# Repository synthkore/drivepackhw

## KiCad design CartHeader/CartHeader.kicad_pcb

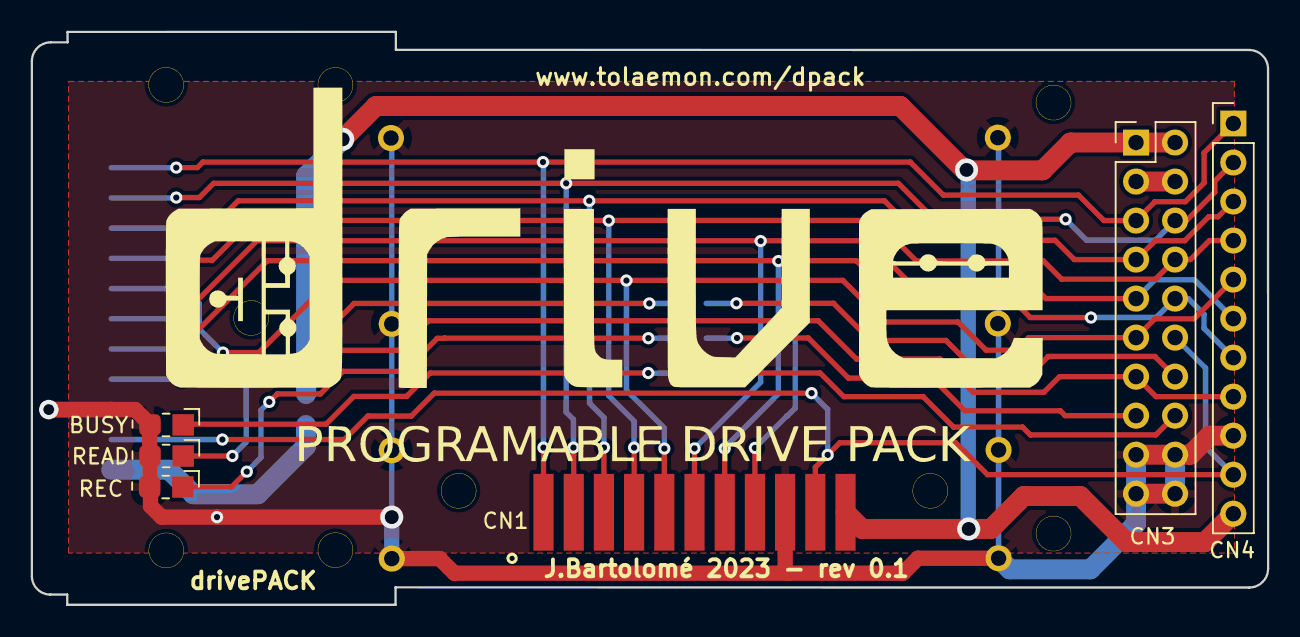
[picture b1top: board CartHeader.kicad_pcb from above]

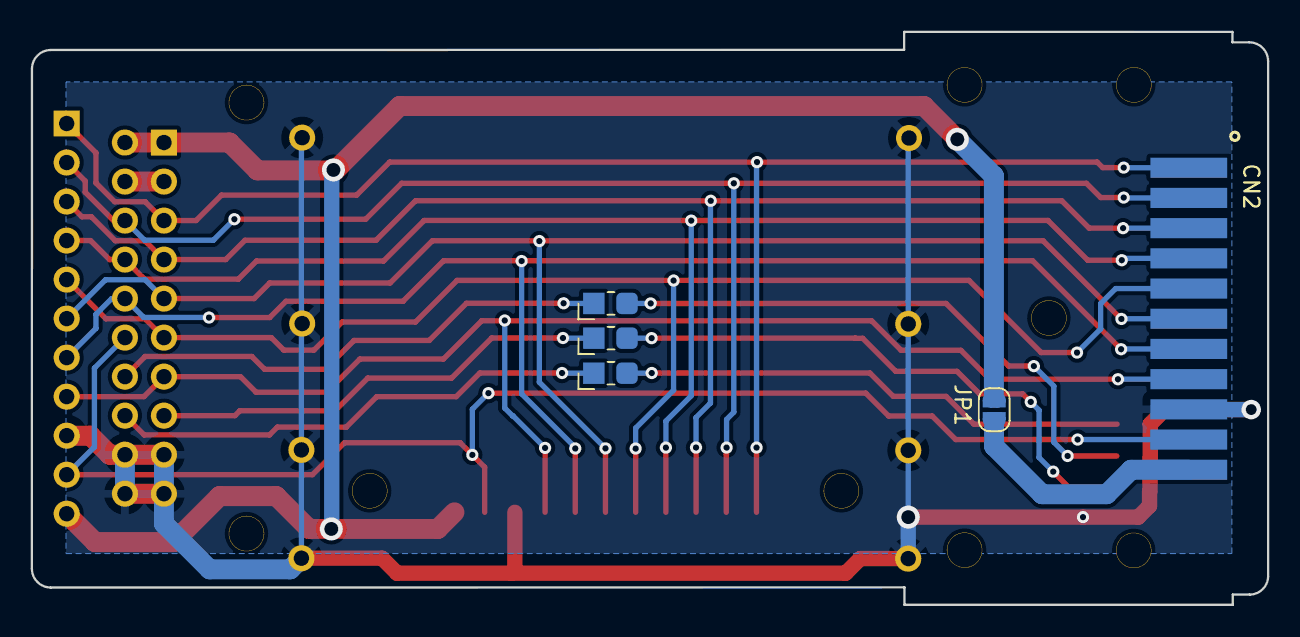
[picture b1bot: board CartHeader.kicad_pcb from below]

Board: 2 copper layers, 80.5 x 37.3 mm, 28 parts (5 on the bottom side), 19 nets.

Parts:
BUSY: LD; SMD_LD_0805_2012Metric
CN1: dumper connector; DrivePackHeaderFemale
CN2: drivePACKconnector; DrivePackHeaderMale
CN3: PinStrip2x10; PinHeader_2x10_P2.54mm_Vertical
CN4: PinStrip11; PinHeader_1x11_P2.54mm_Vertical
CN5, CN6, CN7, CN8, CN9, CN10, CN11, CN12: Pin; PinPad_1x01_P2.54mm_Round
JP1: Jumper; SolderJumper-2_P1.3mm_Open_RoundedPad1.0x1.5mm
MH1, MH2, MH3, MH4, MH5, MH6, MH7, MH8, MH9: MountingHole; MHole_2_25
R1, R2, R3: 150; SMD_R_0805_2012Metric
READ: LD; SMD_LD_0805_2012Metric
REC: LD; SMD_LD_0805_2012Metric

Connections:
/!CS: CN1.10 (nCS), CN2.10 (nCS), CN3.12, CN4.10
/!D0: CN1.4 (nD0), CN2.4 (nD0), CN3.8, CN4.4
/!D1: CN1.3 (nD1), CN2.3 (nD1), CN3.7, CN4.3
/!D2: CN1.2 (nD2), CN2.2 (nD2), CN3.6, CN4.2
/!D3: CN1.1 (nD3), CN2.1 (nD3), CN3.5, CN4.1
/!W\R: CN1.5 (RnW), CN2.5 (RnW), CN3.11, CN4.5
/?: CN1.8 (?), CN2.8 (?), CN3.13, CN4.8
/CLCK1: CN1.6 (CLK1), CN2.6 (CLK1), CN3.9, CN4.6
/CLCK2: CN1.7 (CLK2), CN2.7 (CLK2), CN3.10, CN4.7
/ROM_IO1: CN3.14, R1.1
/ROM_IO2: CN3.15, R2.1
/ROM_IO3: CN3.16, R3.1
GND: BUSY.2, CN1.9 (GND), CN2.9 (GND), CN3.17, CN3.18, CN3.19, CN3.20, CN4.9, CN5.1, CN6.1, CN7.1, CN8.1, CN9.1, CN10.1, CN11.1, CN12.1, READ.2, REC.2
unnamed: CN2.11 (Vcc), JP1.1
unnamed: R1.2, READ.1
unnamed: R2.2, REC.1
unnamed: BUSY.1, R3.2
VCC3.3: CN3.3, CN3.4
VCC5: CN1.11 (Vcc), CN3.1, CN3.2, CN4.11, JP1.2

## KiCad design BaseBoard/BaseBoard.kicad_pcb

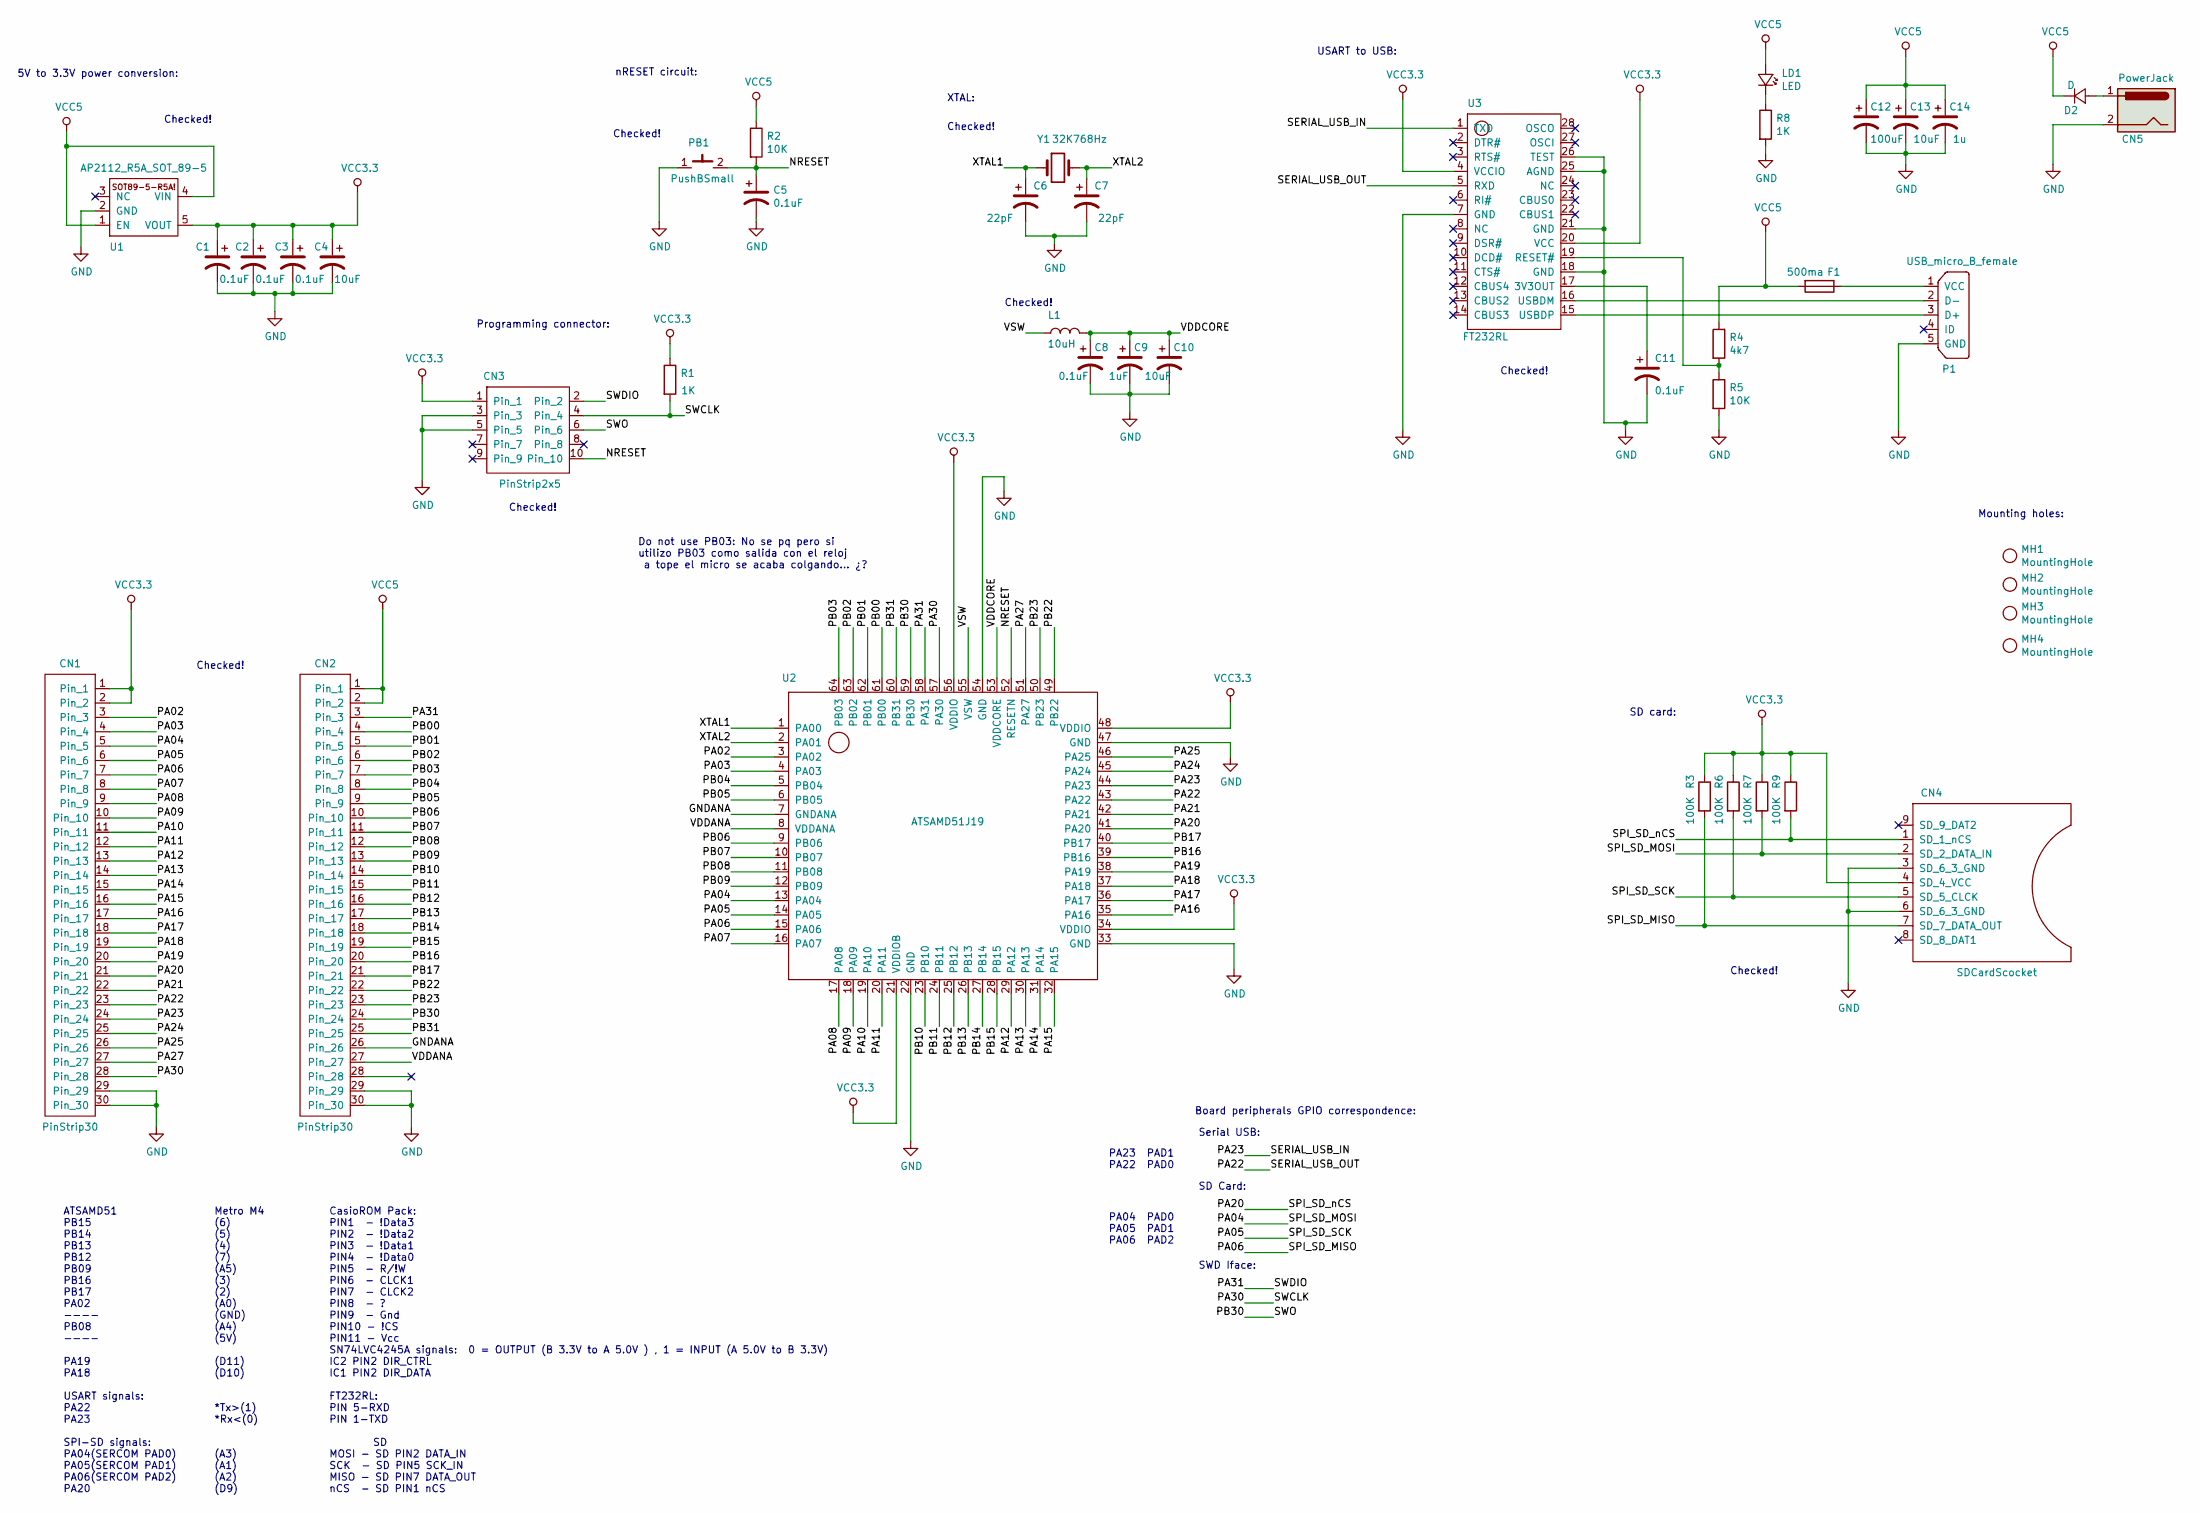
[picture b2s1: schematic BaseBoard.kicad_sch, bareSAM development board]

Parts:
C1, C2, C3, C5, C8, C11: 0.1uF; SMD_C_0805_2012Metric
C4, C10, C13: 10uF; SMD_C_0.5x0.5cm
C6, C7: 22pF; SMD_C_0805_2012Metric
C9: 1uF; SMD_C_0.5x0.5cm
C12: 100uF; SMD_C_0.5x0.5cm
C14: 1u; SMD_C_0.5x0.5cm
CN1, CN2: PinStrip30; PinHeader_1x30_P2.54mm_Vertical
CN3: PinStrip2x5; PinHeader_2x05_P2.54mm_Vertical
CN4: SDCardScocket; SDCard_NoHoles
CN5: PowerJack; PowerFemale
D2: D; D_SOD-123
F1: 500ma; SMD_C_0805_2012Metric
L1: 10uH; SMD_L_4018
LD1: LED; SMD_LD_0805_2012Metric
MH1, MH2, MH3, MH4: MountingHole
P1: USB_micro_B_female; USB_Micro-B_Wuerth_629105150521
PB1: PushBSmall; PushButton
R1, R8: 1K; SMD_R_0805_2012Metric
R2, R5: 10K; SMD_R_0805_2012Metric
R3, R6, R7, R9: 100K; SMD_R_0805_2012Metric
R4: 4k7; SMD_R_0805_2012Metric
U1: AP2112_R5A_SOT_89-5; SOT-89-5_Handsoldering
U2: ATSAMD51J19; TQFP-64-1EP_10x10mm_P0.5mm_EP8x8mm
U3: FT232RL; SSOP-28_5.3x10.2mm_P0.65mm
Y1: 32K768Hz; SMD_XTAL_3.4x2.7max

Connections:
/GNDANA: CN2.26, U2.7 (GNDANA)
/NRESET: C5.1, CN3.10, PB1.2, R2.2, U2.52 (RESETN)
/PA02: CN1.3, U2.3 (PA02)
/PA03: CN1.4, U2.4 (PA03)
/PA04: CN1.5, CN4.2 (SD_2_DATA_IN), R7.2, U2.13 (PA04)
/PA05: CN1.6, CN4.5 (SD_5_CLCK), R6.2, U2.14 (PA05)
/PA06: CN1.7, CN4.7 (SD_7_DATA_OUT), R3.2, U2.15 (PA06)
/PA07: CN1.8, U2.16 (PA07)
/PA08: CN1.9, U2.17 (PA08)
/PA09: CN1.10, U2.18 (PA09)
/PA10: CN1.11, U2.19 (PA10)
/PA11: CN1.12, U2.20 (PA11)
/PA12: CN1.13, U2.29 (PA12)
/PA13: CN1.14, U2.30 (PA13)
/PA14: CN1.15, U2.31 (PA14)
/PA15: CN1.16, U2.32 (PA15)
/PA16: CN1.17, U2.35 (PA16)
/PA17: CN1.18, U2.36 (PA17)
/PA18: CN1.19, U2.37 (PA18)
/PA19: CN1.20, U2.38 (PA19)
/PA20: CN1.21, CN4.1 (SD_1_nCS), R9.2, U2.41 (PA20)
/PA21: CN1.22, U2.42 (PA21)
/PA22: CN1.23, U2.43 (PA22), U3.5 (RXD)
/PA23: CN1.24, U2.44 (PA23), U3.1 (TXD)
/PA24: CN1.25, U2.45 (PA24)
/PA25: CN1.26, U2.46 (PA25)
/PA27: CN1.27, U2.51 (PA27)
/PA30: CN1.28, CN3.4, R1.2, U2.57 (PA30)
/PA31: CN2.3, CN3.2, U2.58 (PA31)
/PB00: CN2.4, U2.61 (PB00)
/PB01: CN2.5, U2.62 (PB01)
/PB02: CN2.6, U2.63 (PB02)
/PB03: CN2.7, U2.64 (PB03)
/PB04: CN2.8, U2.5 (PB04)
/PB05: CN2.9, U2.6 (PB05)
/PB06: CN2.10, U2.9 (PB06)
/PB07: CN2.11, U2.10 (PB07)
/PB08: CN2.12, U2.11 (PB08)
/PB09: CN2.13, U2.12 (PB09)
/PB10: CN2.14, U2.23 (PB10)
/PB11: CN2.15, U2.24 (PB11)
/PB12: CN2.16, U2.25 (PB12)
/PB13: CN2.17, U2.26 (PB13)
/PB14: CN2.18, U2.27 (PB14)
/PB15: CN2.19, U2.28 (PB15)
/PB16: CN2.20, U2.39 (PB16)
/PB17: CN2.21, U2.40 (PB17)
/PB22: CN2.22, U2.49 (PB22)
/PB23: CN2.23, U2.50 (PB23)
/PB30: CN2.24, CN3.6, U2.59 (PB30)
/PB31: CN2.25, U2.60 (PB31)
/VDDANA: CN2.27, U2.8 (VDDANA)
/VDDCORE: C8.1, C9.1, C10.1, L1.1, U2.53 (VDDCORE)
/VSW: L1.2, U2.55 (VSW)
/XTAL1: C6.1, U2.1 (PA00), Y1.1
/XTAL2: C7.1, U2.2 (PA01), Y1.2
GND: C1.2, C2.2, C3.2, C4.2, C5.2, C6.2, C7.2, C8.2, C9.2, C10.2, C11.2, C12.2, C13.2, C14.2, CN1.29, CN1.30, CN2.29, CN2.30, CN3.3, CN3.5, CN4.3 (SD_6_3_GND), CN4.6 (SD_6_3_GND), CN5.2, P1.5 (GND), PB1.1, R5.2, R8.2, U1.2 (GND), U2.22 (GND), U2.33 (GND), U2.47 (GND), U2.54 (GND), U3.7 (GND), U3.18 (GND), U3.21 (GND), U3.25 (AGND), U3.26 (TEST)
unnamed: C11.1, U3.17 (3V3OUT)
unnamed: CN5.1, D2.1
unnamed: F1.1, P1.1 (VCC)
unnamed: LD1.2, R8.1
unnamed: P1.2 (D-), U3.16 (USBDM)
unnamed: P1.3 (D+), U3.15 (USBDP)
unnamed: R4.2, R5.1, U3.19 (RESET#)
VCC3.3: C1.1, C2.1, C3.1, C4.1, CN1.1, CN1.2, CN3.1, CN4.4 (SD_4_VCC), R1.1, R3.1, R6.1, R7.1, R9.1, U1.5 (VOUT), U2.21 (VDDIOB), U2.34 (VDDIO), U2.48 (VDDIO), U2.56 (VDDIO), U3.4 (VCCIO), U3.20 (VCC)
VCC5: C12.1, C13.1, C14.1, CN2.1, CN2.2, D2.2, F1.2, LD1.1, R2.1, R4.1, U1.1 (EN), U1.4 (VIN)

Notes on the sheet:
XTAL:
PA04 PAD0 PA05 PAD1 PA06 PAD2
Do not use PB03: No se pq pero si utilizo PB03 como salida con el reloj a tope el micro se acaba colgando... ¿?
Mounting holes:
Checked!
Metro M4 (6) (5) (4) (7) (A5) (3) (2) (A0) (GND) (A4) (5V) (D11) (D10) *Tx>(1) *Rx<(0) (A3) (A1) (A2) (D9)
CasioROM Pack: PIN1 - !Data3 PIN2 - !Data2 PIN3 - !Data1 PIN4 - !Data0 PIN5 - R/!W PIN6 - CLCK1 PIN7 - CLCK2 PIN8 - ? PIN9 - Gnd PIN10 - !CS PIN11 - Vcc SN74LVC4245A signals: 0 = OUTPUT (B 3.3V to A 5.0V ) , 1 = INPUT (A 5.0V to B 3.3V) IC2 PIN2 DIR_CTRL IC1 PIN2 DIR_DATA FT232RL: PIN 5-RXD PIN 1-T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
Board peripherals GPIO correspondence:
5V to 3.3V power conversion:
SWD Iface:
PA23 PAD1 PA22 PAD0
Serial USB:
USART to USB:
Programming connector:
SD Card:
ATSAMD51 PB15 PB14 PB13 PB12 PB09 PB16 PB17 PA02 ---- PB08 ---- PA19 PA18 USART signals: PA22 PA23 SPI-SD signals: PA04(SERCOM PAD0) PA05(SERCOM PAD1) PA06(SERCOM PAD2) PA20
nRESET circuit:
SD card:

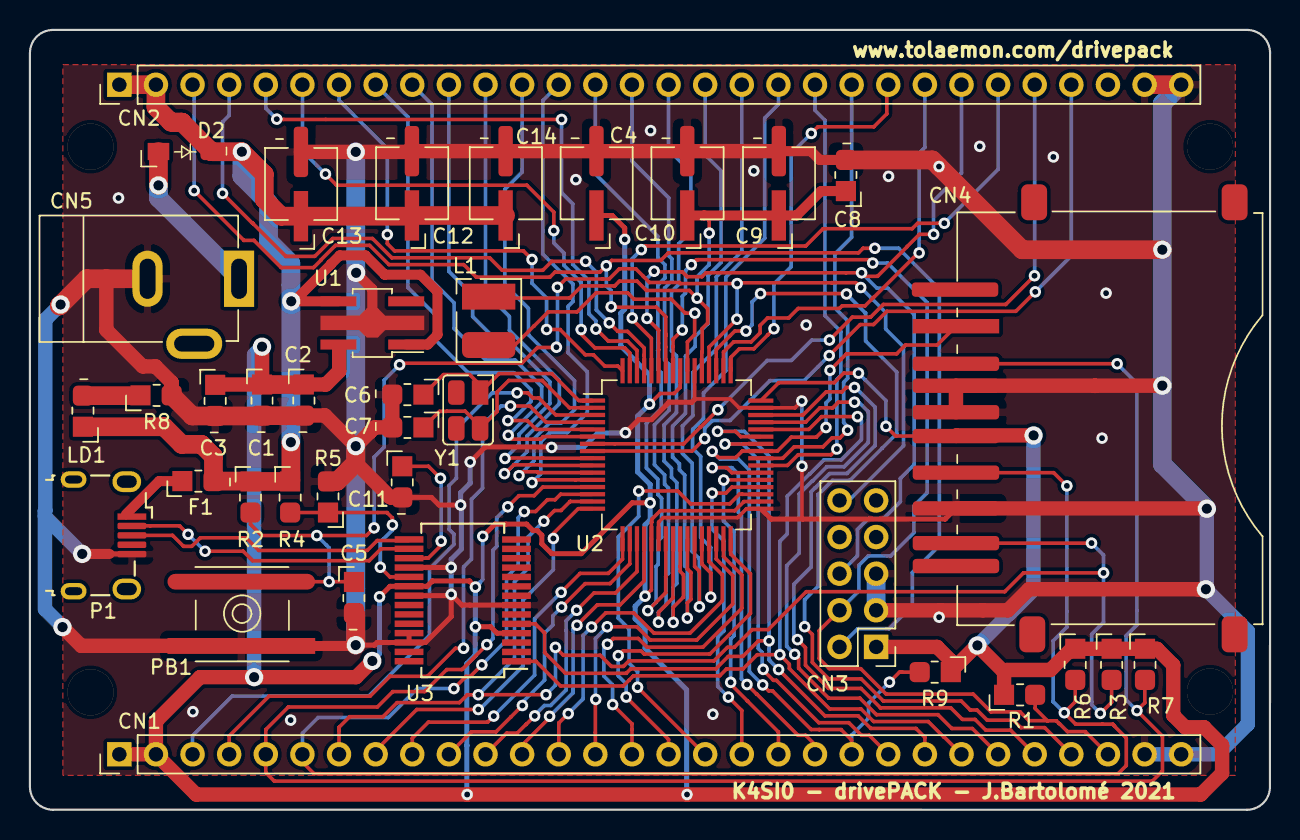
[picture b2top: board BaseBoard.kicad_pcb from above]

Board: 2 copper layers, 86.0 x 54.1 mm, 42 parts (0 on the bottom side), 66 nets.

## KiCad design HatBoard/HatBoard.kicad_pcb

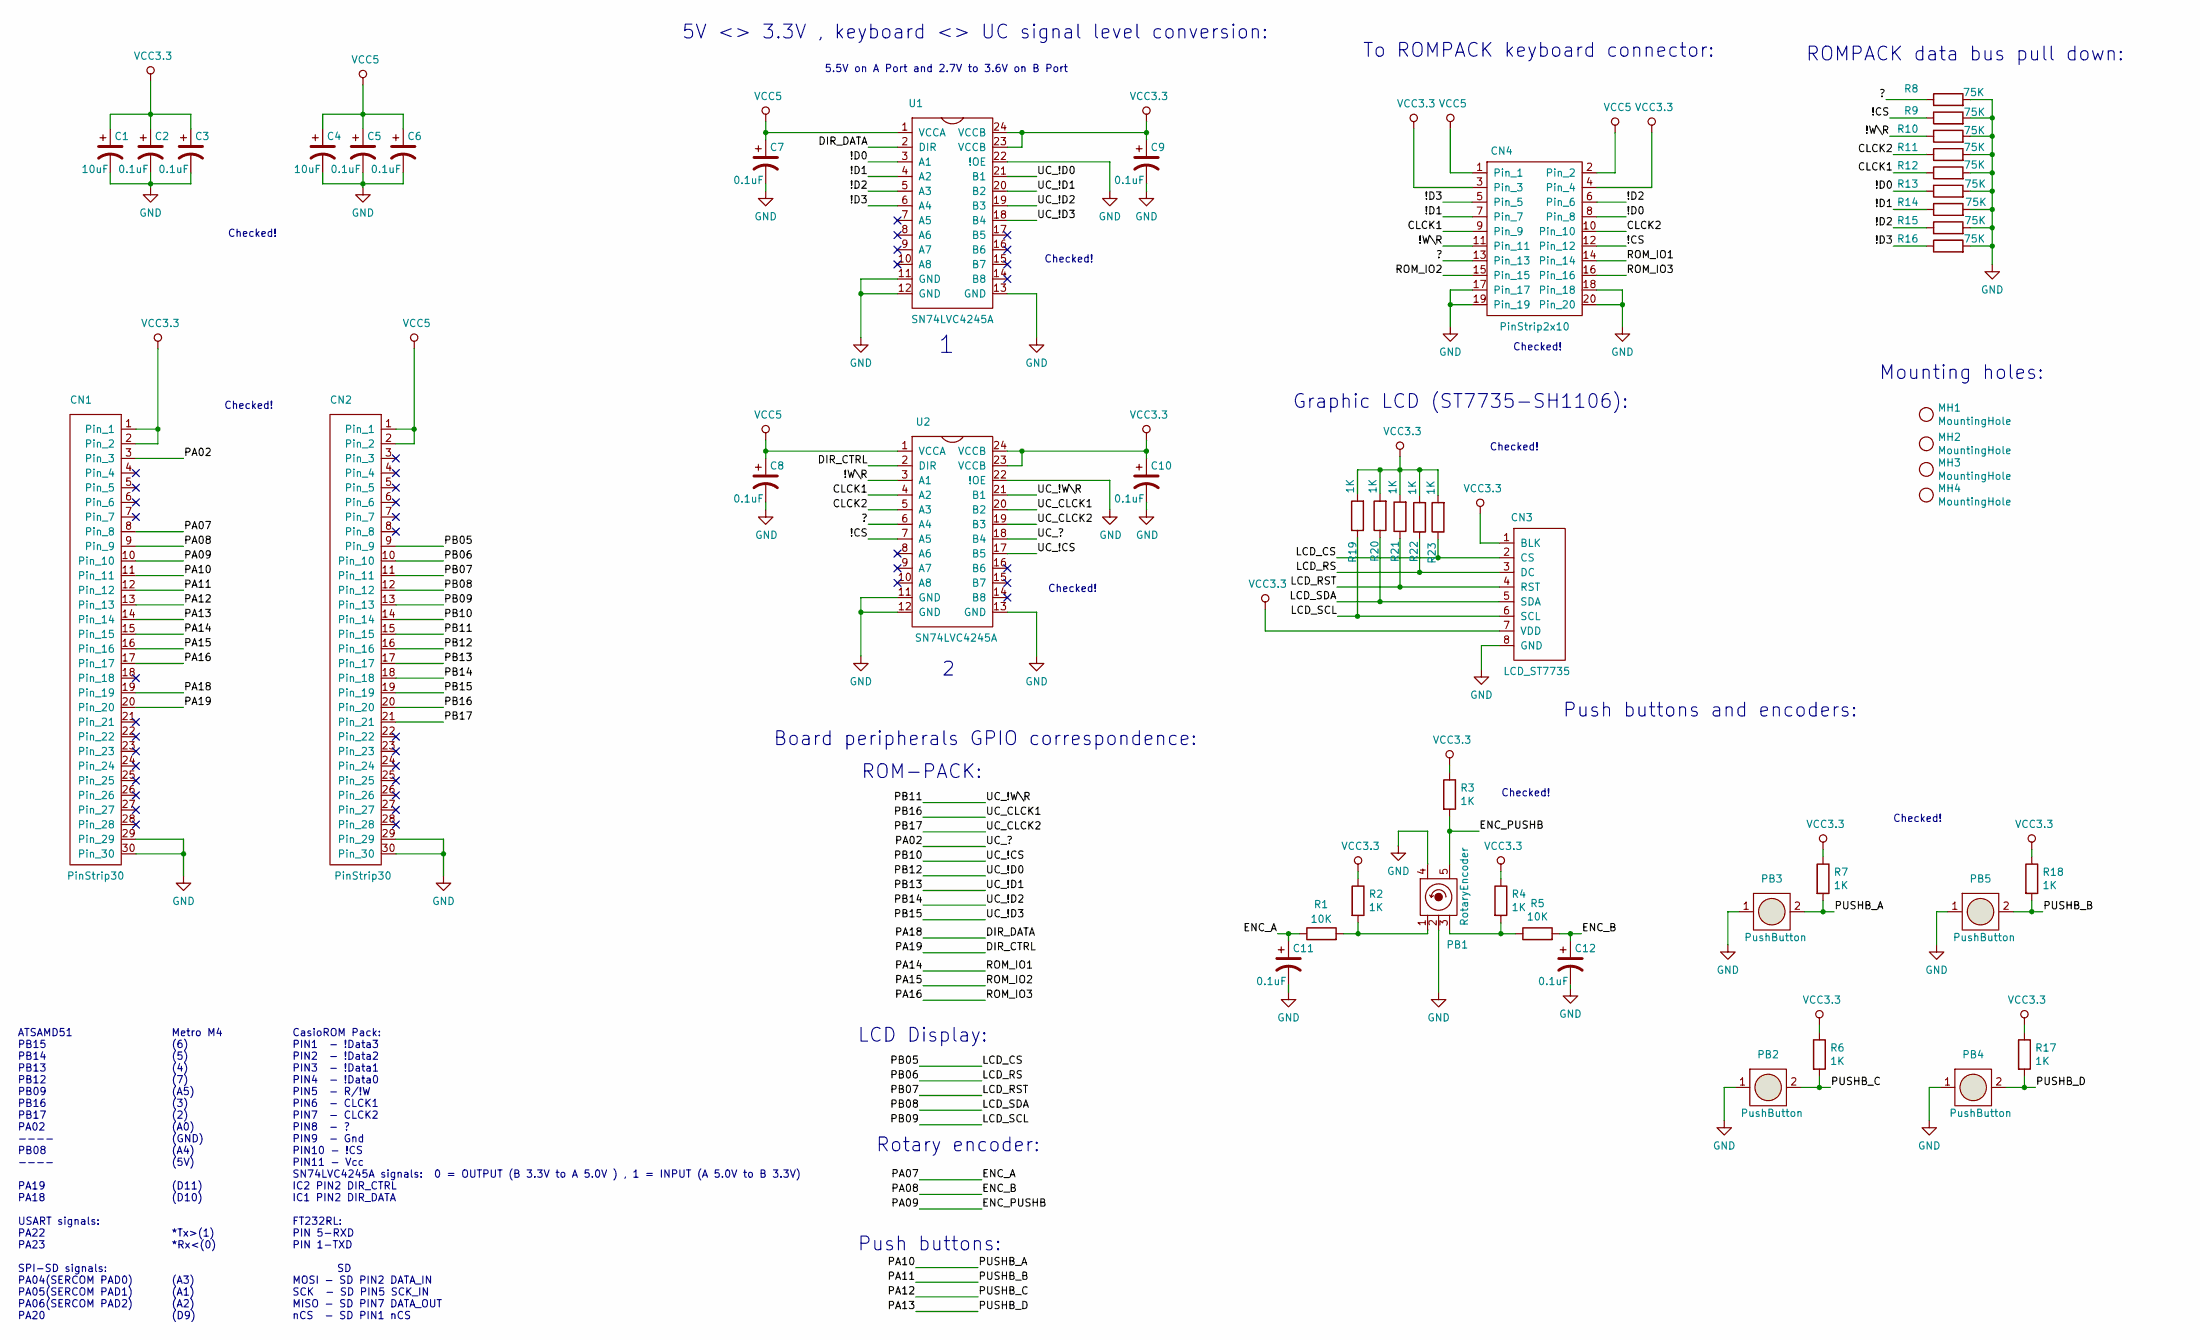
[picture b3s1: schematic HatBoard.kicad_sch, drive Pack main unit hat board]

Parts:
C1, C4: 10uF; SMD_C_0.5x0.5cm
C2, C3, C5, C6, C7, C8, C9, C10, C11, C12: 0.1uF; SMD_C_0805_2012Metric
CN1, CN2: PinStrip30; PinHeader_1x30_P2.54mm_Vertical
CN3: LCD_ST7735
CN4: PinStrip2x10; PinHeader_2x10_P2.54mm_Vertical
MH1, MH2, MH3, MH4: MountingHole
PB1: RotaryEncoder; EncoderPushButton
PB2, PB3, PB4, PB5: PushButton; PushButtonBig
R1, R5: 10K; SMD_R_0805_2012Metric
R2, R3, R4, R6, R7, R17, R18, R19, R20, R21, R22, R23: 1K; SMD_R_0805_2012Metric
R8, R9, R10, R11, R12, R13, R14, R15, R16: 75K; SMD_R_0805_2012Metric
U1, U2: SN74LVC4245A; SSOP-24_5.3x8.2mm_P0.65mm

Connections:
/!CS: CN4.12, R9.1, U2.7 (A5)
/!D0: CN4.8, R13.1, U1.3 (A1)
/!D1: CN4.7, R14.1, U1.4 (A2)
/!D2: CN4.6, R15.1, U1.5 (A3)
/!D3: CN4.5, R16.1, U1.6 (A4)
/!W\R: CN4.11, R10.1, U2.3 (A1)
/?: CN4.13, R8.1, U2.6 (A4)
/CLCK1: CN4.9, R12.1, U2.4 (A2)
/CLCK2: CN4.10, R11.1, U2.5 (A3)
/DIR_CTRL: CN1.20, U2.2 (DIR)
/DIR_DATA: CN1.19, U1.2 (DIR)
/ENC_A: C11.1, CN1.8, R1.1
/ENC_B: C12.1, CN1.9, R5.2
/ENC_PUSHB: CN1.10, PB1.5, R3.2
/LCD_CS: CN2.9, CN3.2 (CS), R23.1
/LCD_RS: CN2.10, CN3.3 (DC), R22.1
/LCD_RST: CN2.11, CN3.4 (RST), R21.1
/LCD_SCL: CN2.13, CN3.6 (SCL), R19.1
/LCD_SDA: CN2.12, CN3.5 (SDA), R20.1
/PA02: CN1.3, U2.18 (B4)
/PA10: CN1.11, PB3.2, R7.2
/PA11: CN1.12, PB5.2, R18.2
/PA12: CN1.13, PB2.2, R6.2
/PA13: CN1.14, PB4.2, R17.2
/PA14: CN1.15, CN4.14
/PA15: CN1.16, CN4.15
/PA16: CN1.17, CN4.16
/PB10: CN2.14, U2.17 (B5)
/PB11: CN2.15, U2.21 (B1)
/PB12: CN2.16, U1.21 (B1)
/PB13: CN2.17, U1.20 (B2)
/PB14: CN2.18, U1.19 (B3)
/PB15: CN2.19, U1.18 (B4)
/PB16: CN2.20, U2.20 (B2)
/PB17: CN2.21, U2.19 (B3)
GND: C1.2, C2.2, C3.2, C4.2, C5.2, C6.2, C7.2, C8.2, C9.2, C10.2, C11.2, C12.2, CN1.29, CN1.30, CN2.29, CN2.30, CN3.8 (GND), CN4.17, CN4.18, CN4.19, CN4.20, PB1.2, PB1.4, PB2.1, PB3.1, PB4.1, PB5.1, R8.2, R9.2, R10.2, R11.2, R12.2, R13.2, R14.2, R15.2, R16.2, U1.11 (GND), U1.12 (GND), U1.13 (GND), U1.22 (!OE), U2.11 (GND), U2.12 (GND), U2.13 (GND), U2.22 (!OE)
unnamed: PB1.1, R1.2, R2.2
unnamed: PB1.3, R4.2, R5.1
VCC3.3: C1.1, C2.1, C3.1, C9.1, C10.1, CN1.1, CN1.2, CN3.1 (BLK), CN3.7 (VDD), CN4.3, CN4.4, R2.1, R3.1, R4.1, R6.1, R7.1, R17.1, R18.1, R19.2, R20.2, R21.2, R22.2, R23.2, U1.23 (VCCB), U1.24 (VCCB), U2.23 (VCCB), U2.24 (VCCB)
VCC5: C4.1, C5.1, C6.1, C7.1, C8.1, CN2.1, CN2.2, CN4.1, CN4.2, U1.1 (VCCA), U2.1 (VCCA)

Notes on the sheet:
LCD Display:
Checked!
Metro M4 (6) (5) (4) (7) (A5) (3) (2) (A0) (GND) (A4) (5V) (D11) (D10) *Tx>(1) *Rx<(0) (A3) (A1) (A2) (D9)
ROM-PACK:
Rotary encoder:
Push buttons and encoders:
Board peripherals GPIO correspondence:
Mounting holes:
CasioROM Pack: PIN1 - !Data3 PIN2 - !Data2 PIN3 - !Data1 PIN4 - !Data0 PIN5 - R/!W PIN6 - CLCK1 PIN7 - CLCK2 PIN8 - ? PIN9 - Gnd PIN10 - !CS PIN11 - Vcc SN74LVC4245A signals: 0 = OUTPUT (B 3.3V to A 5.0V ) , 1 = INPUT (A 5.0V to B 3.3V) IC2 PIN2 DIR_CTRL IC1 PIN2 DIR_DATA FT232RL: PIN 5-RXD PIN 1-T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
Graphic LCD (ST7735-SH1106):
ROMPACK data bus pull down:
To ROMPACK keyboard connector:
5V <> 3.3V , keyboard <> UC signal level conversion:
ATSAMD51 PB15 PB14 PB13 PB12 PB09 PB16 PB17 PA02 ---- PB08 ---- PA19 PA18 USART signals: PA22 PA23 SPI-SD signals: PA04(SERCOM PAD0) PA05(SERCOM PAD1) PA06(SERCOM PAD2) PA20
Push buttons:
5.5V on A Port and 2.7V to 3.6V on B Port

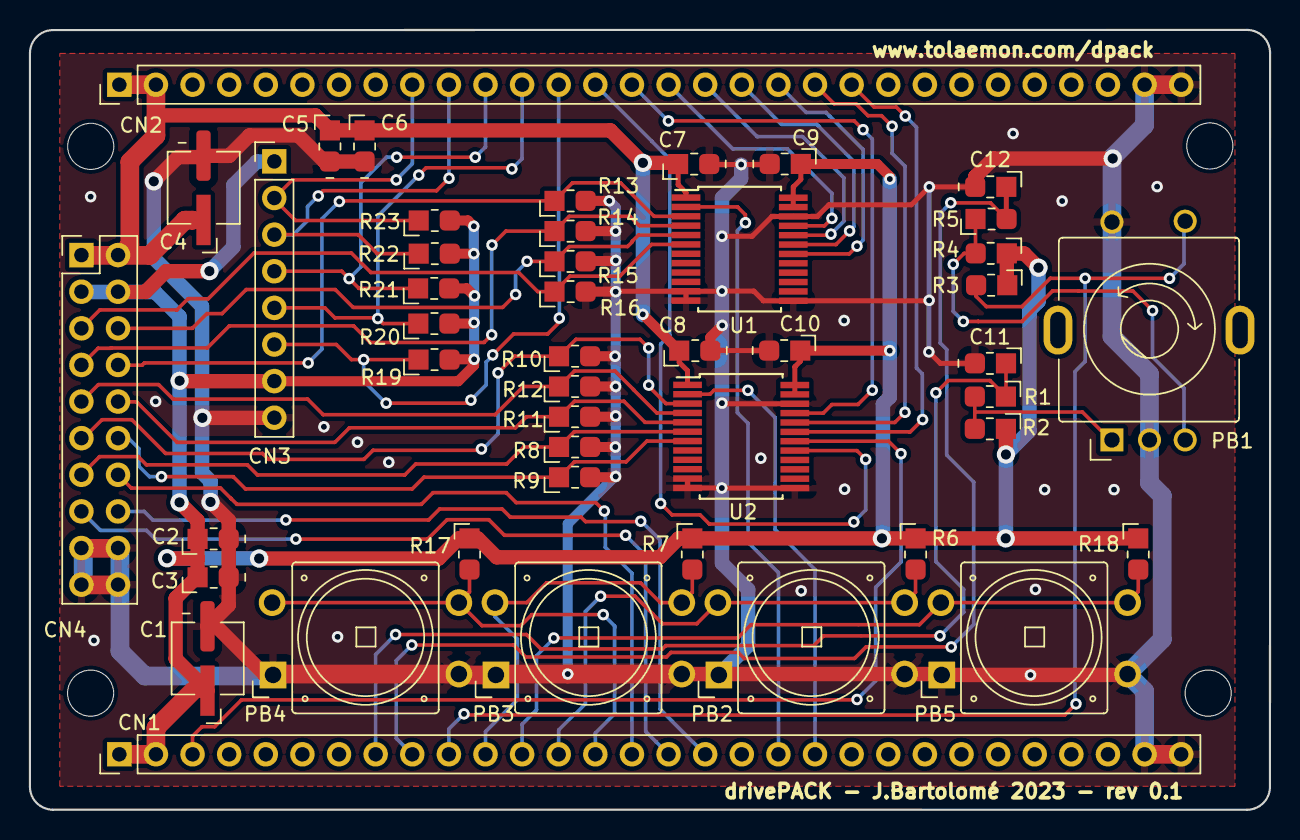
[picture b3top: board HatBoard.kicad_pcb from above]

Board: 2 copper layers, 86.0 x 54.1 mm, 50 parts (0 on the bottom side), 40 nets.

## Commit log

2023-12-17 drivePack revised schematics and PCBs
2024-01-06 Added JTAG to SWD equivalence in BaseBoard schematics
2025-04-04 Added the header base board to the repository.
2025-04-04 Minor corrections in the comments.
